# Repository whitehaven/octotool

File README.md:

# `octotool`

An attempt to make a PCB Octopus Tester, aka VI curve tracer, for use with my oscilloscope. (Siglent SDS 1104X-E)

Started thinking thus:

But now, more thinking about it this way:

Components Included:
- Kicad PCB: [text](octotool/octotool.kicad_pro)

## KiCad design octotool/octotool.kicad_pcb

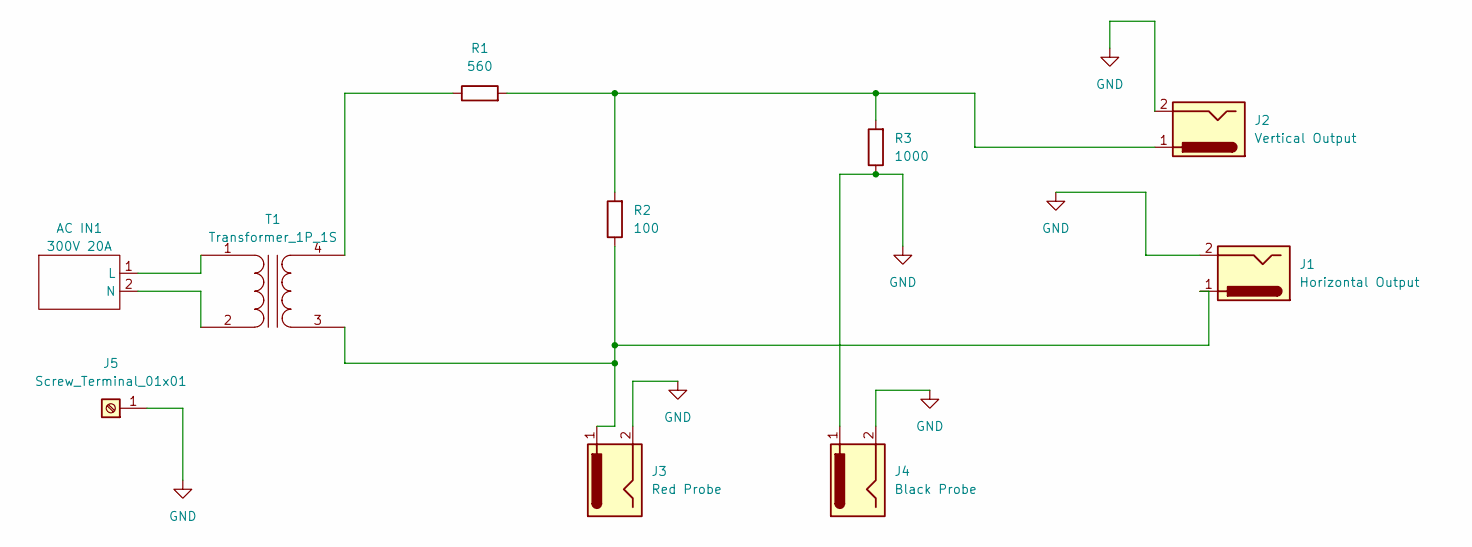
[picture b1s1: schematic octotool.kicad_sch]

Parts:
AC IN1: 300V 20A; XY2500R Receptacle
J1: Horizontal Output; BarrelJack_CLIFF_FC681465S_SMT_Horizontal
J2: Vertical Output; BarrelJack_CLIFF_FC681465S_SMT_Horizontal
J3: Red Probe; BarrelJack_CLIFF_FC681465S_SMT_Horizontal
J4: Black Probe; BarrelJack_CLIFF_FC681465S_SMT_Horizontal
J5: Screw_Terminal_01x01; TerminalBlock_MetzConnect_360271_1x01_Horizontal_ScrewM3.0_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
R1: 560; R_1020_2550Metric_Pad1.33x5.20mm_HandSolder
R2: 100; R_1020_2550Metric_Pad1.33x5.20mm_HandSolder
R3: 1000; R_1020_2550Metric_Pad1.33x5.20mm_HandSolder
T1: Transformer_1P_1S; Transformer_Coilcraft_CST1

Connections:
GND: J1.2, J2.2, J3.2, J4.1, J4.2, J5.1, R3.1
unnamed: AC IN1.1 (L), T1.1 (AA)
unnamed: AC IN1.2 (N), T1.2 (AB)
unnamed: J2.1, R1.2, R2.2, R3.2
unnamed: J1.1, J3.1, R2.1, T1.3 (SA)
unnamed: R1.1, T1.4 (SB)

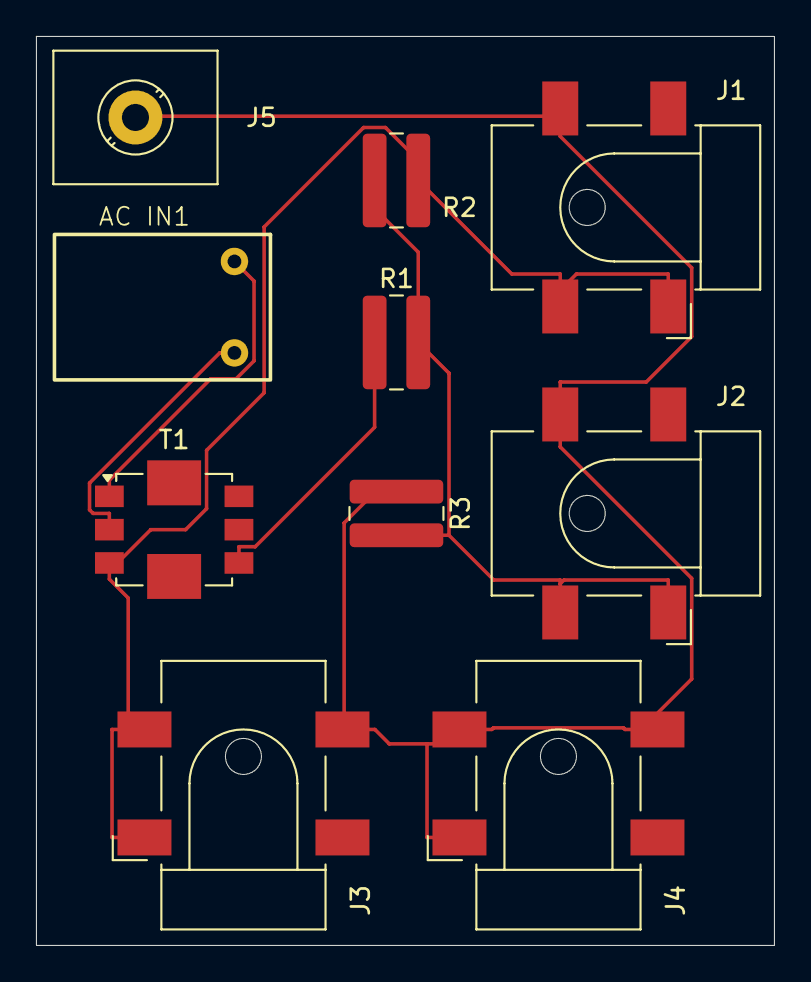
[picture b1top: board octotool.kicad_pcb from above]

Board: 2 copper layers, 41.0 x 50.5 mm, 10 parts (0 on the bottom side), 6 nets.

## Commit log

2024-06-19 init primary files
2024-06-19 init symbol library octotool
2024-06-19 init octotool footprint
2024-06-19 optimize .gitignore with online pre-compiled exclusions
2024-06-19 add previously missed config files
2024-06-19 add schematics
2024-06-19 Create LICENSE
2024-06-19 describe project
